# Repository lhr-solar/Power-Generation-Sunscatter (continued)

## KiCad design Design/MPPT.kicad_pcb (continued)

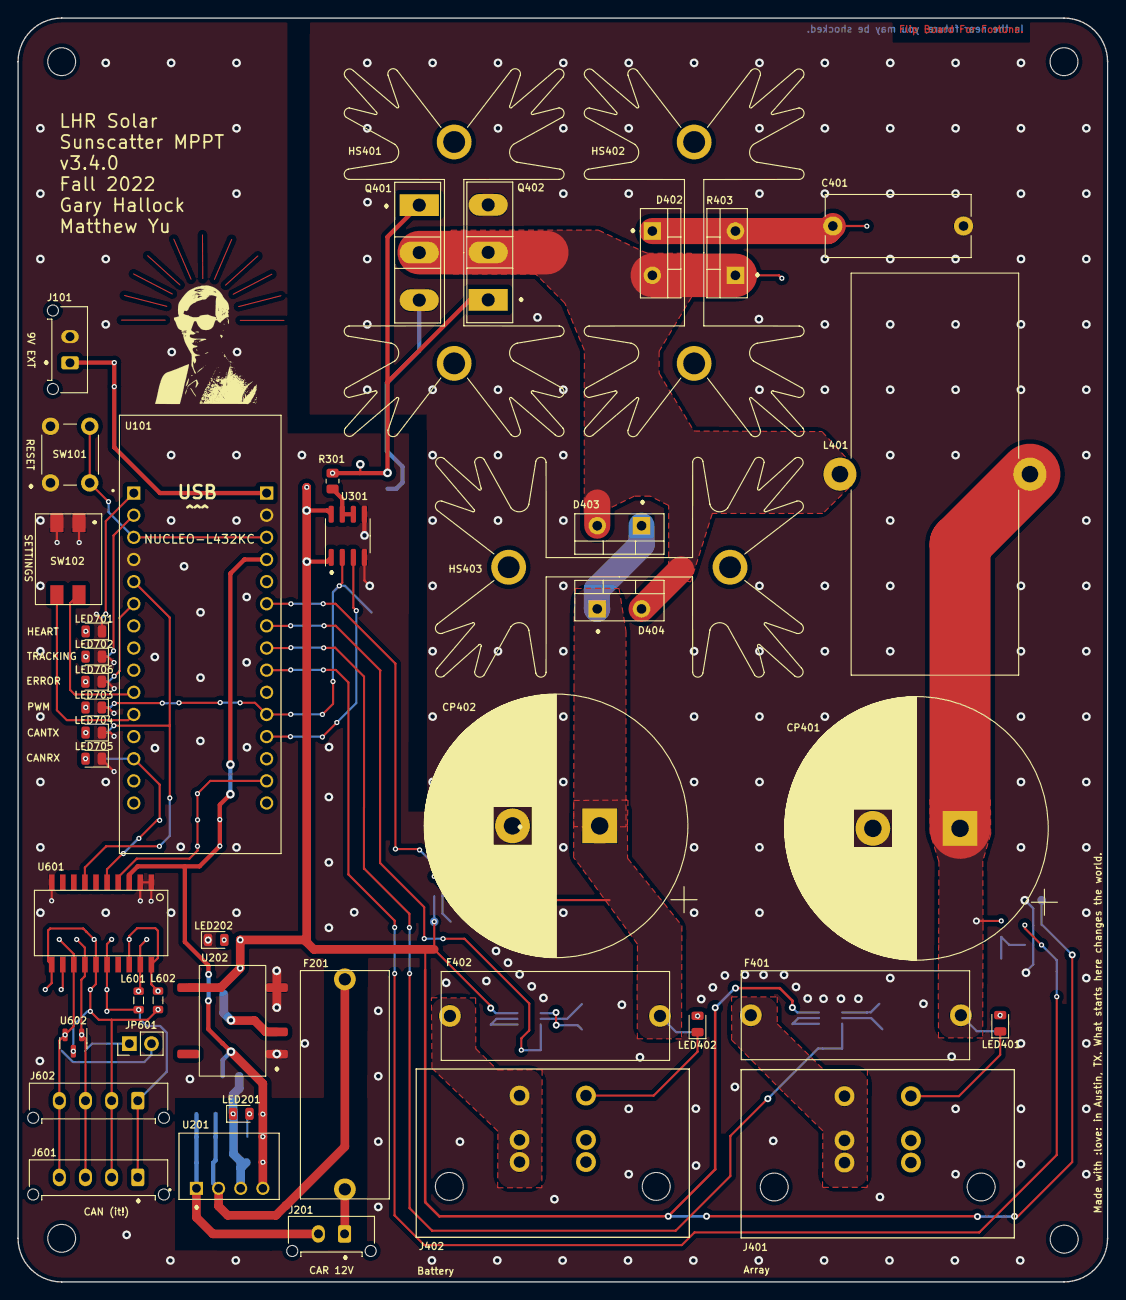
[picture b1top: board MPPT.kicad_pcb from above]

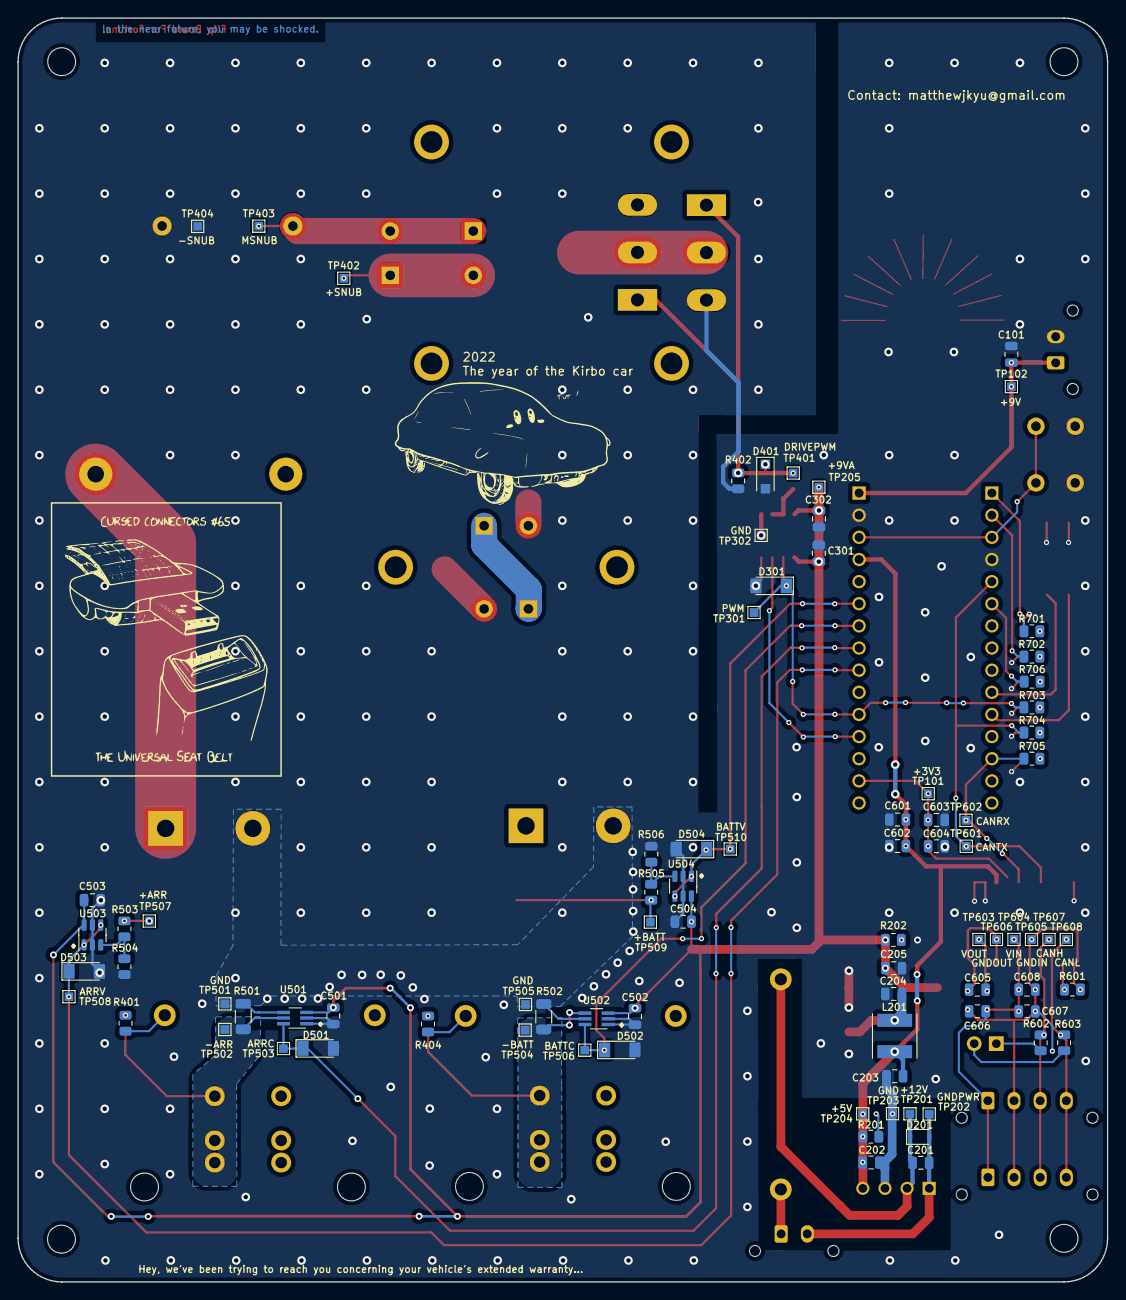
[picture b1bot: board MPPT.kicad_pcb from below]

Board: 2 copper layers, 125.0 x 145.0 mm, 131 parts (83 on the bottom side), 54 nets.

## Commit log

2020-08-02 Set up for own repo
2020-09-05 added unity gain op amp buffer to voltage sensors
2020-09-06 added back in heatsinks and generated gerber.
2020-10-03 Adds QuAC
2020-12-07 Major MPPT Board update. Overhaul of layout, and cleanup of the schematic. Added further documentation and updated instructions in the README. Added unity gain op amp for voltage sensors.
2020-12-13 Finalized board layout.
2020-12-13 savestate
2020-12-13 Updated README.md.
2020-12-14 Updated README and some little board positionings.
2020-12-14 Major MPPT Board overhaul. Schematic advanced to Rev 3.2. Layout advanced to Rev 1.3. README and documentation updated. Parts list synchronized, standardized, and referenced.
2020-12-18 Addressed review.
2021-01-14 minor fixes and step rebuild.
2021-02-13 Rotated user comments on the layout and added PDFs of the version schematic and layout.
2021-05-27 Added board improvement suggestion for layout revision 1.3.0.
2022-02-04 schematic and layout revision.
2022-02-04 secondary ground with via stitching
2022-02-11 Revisions on schematic and layout. See notes in the schematic for changes.
2022-02-11 regenerated outputs and labeled output zip.
2022-02-11 README update.
2022-02-17 gerber rebuild for JLPCB errors
2022-04-01 gerber savestate
2022-06-03 v3.3.1 changes.
2022-06-07 Version 3.4.0.
    Repo structure has significantly been updated for better navigation and exploration.
    Schematic has been broken into hierarchical sheets, all components have been reannotated.
    All schematic warnings have been expunged.
    Layout silkscreen has been updated to comply with new annotation.
    Datasheets for components have been added.
    ORDERING.md instructions have been updated. Now includes SMT/SMD assembly. And pictures.
2022-07-17 documentation for v3.4.0.
2023-05-20 savestate 3.4.0
2023-05-20 restructuring, pulling in fw from power-gen repo
2023-07-17 pull in latest from main, hopefully no changes here
2023-11-18 Updated CAN test simulating can writes for 3 MPPTs, 8 RTDs, & 2 Irrad sensors
    For LV Integration
2023-12-02 Update version & date
